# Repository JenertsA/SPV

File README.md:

# SPV
Darbi un piemēri Siguldas pilsētas vidusskolas Robtou tehnoloģiju novirzienam

## Ko šeit var atrast?
Pakāpeniski šeit tiks ievietoti darbi un piemēri, kas saistīti ar:
- elektornikas pamatiem
- Arduino programmēšanu
- spiesto plašu izstrādi Eagle programmā
- vienkāršu iekārtu izstrādi

jebkurš interesents ir lapini aicināts piedāvāt savus uzlabojumus un ieteikumus materiāliem, kas šeit atrodami

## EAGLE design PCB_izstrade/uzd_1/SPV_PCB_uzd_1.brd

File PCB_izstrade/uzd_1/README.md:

# Uzdevums   

Lai atvieglotu pirmās spiestās plates izstrādi Tev jau ir dota strādājoša shēma, kurā
izmantotas zināmi un pārbaudīti komponenšu *footprint*. Iekārta ir pavisam vienārš divu tranzistoru __multivibrators__.

Tev jāizgatavo spiestā plate cilvēkeim, kas __grib iemācīties lodēt__, tāpēc uz plates tiek lietotas lielas, *THD* detaļas.
Izvietotjot kompoenetes ņem vērā to, ka tās lodēs pilnīgi dažadi cilvēki,
dažādos vecumos un ar dažādām prasmēm. Lai salodētā iekārta nebūtu vienkārši izmetama, __izdomā tai interesantu formu__, 
ievieto atbilstoša izmēra urbumu un paredzi komonenšu izvietojumu tā, lai t __varētu lietot kā atslēgas piekariņu__.

## nosacījumi
- plate ir divu slāņu (1p.)
- platei ir neregulāra forma, kas iekļaujas izmēros (3p.)
- ir izpldīts uzdevums, kas atrodams .sch failā kā teksts (3p.)
- ir lietots jēgpilns celiņu platums, kura izmērs ir metrisks (2p.)
- *silkscreen* norādi gadu, kad izstrādāta plate(1p.)
- *silkscreen* atrodams autora vārds vai izdomāts logo (2p.)
- uzaksti, kas atrodas uz *silkscreen* ir izkārtoti un tādā izmērā, kas palīdz cilvēkam ievietot pareizi detaļas (3p.)
- platē tiek lietoti *poligoni*, kas savieno detaļas(2p.)
- celiņi uz plates vilki sistemātiski, lietojot 45° leņķi (3p.)

### papildus uzdevumi
Starp Eagle un Fusion 360 pastāv iesēja savienot projektus. </br>
Ievieto jaunizveidoto plati Fusion360 un uztaisīt detalizētu modeli
kā piekariņš izskatīsies realitātē 

Sagatavo *GERBER* failus pirkš ražotāja

Izveido pirmās reizes pamācību cilvēkam, kas mēģināt lodēt Tavu piekariņu, kas kur jāsprauž un kā kas jādara. 

### paturi prātā
- platei jābūt nelielai, bet ne tika mazai, lai to ir grūti lodēt (iekļaujies 30x30 mm, bet ne lielāku kā 60x30 mm)
- attālumam starp komponentēm jābūt tik lielam, lai, lodējot tās, samazinātu risku izveidot *solder bridge*
- Tev nepieciešami abi faili, gan .sch, gan .brd. Starp tiem pastāv sasaiste, kas lieti noder plates izstrādē.

### *lietotie termini*

*__footprint__* - urbumi vai laukumu izmērs un novietojums konkrētajai detaļa, lai tā varētu tikt montēta platē.

*__THD__* - no angļu valodas *Through-hole technology/devices* detaļas, kas tiek montētas urbumos. 

*__silkscreen__* - uzraksti, kas, parasti baltā krāsā, uzdrukāti uz plates. Tie tiek lietoti, lai marķētu detļau novietojumu, nosaukumu,
retāk detaļu vērtībām. Silkscreens tiek lietotas arī, lai piešķirtu platēm unikālāku izskatu. 

*__poligoni__* - vara pildījumi platē, ar kuru palīdzibu tiek aizstāta viena vai vairāku celiņu vilkšana. Tipiski ir visu plates varu izmantot kā lielu zemes poligonu - *ground plane*

*__GERBER__* - failu kopums, ko nosūta ražotājam, kas izgatavo plates. gerber faili ir de facto standarta faili, kurus atvērs jebkurš ražotājs jebkurā veitā un spēs sagatavot plati ražošanai.

*__solder bridge__* - lodējot divus blakus esošus kontaktus, alva starp lodējumiem saplūst un veido nevēlamu īssavienojumu.

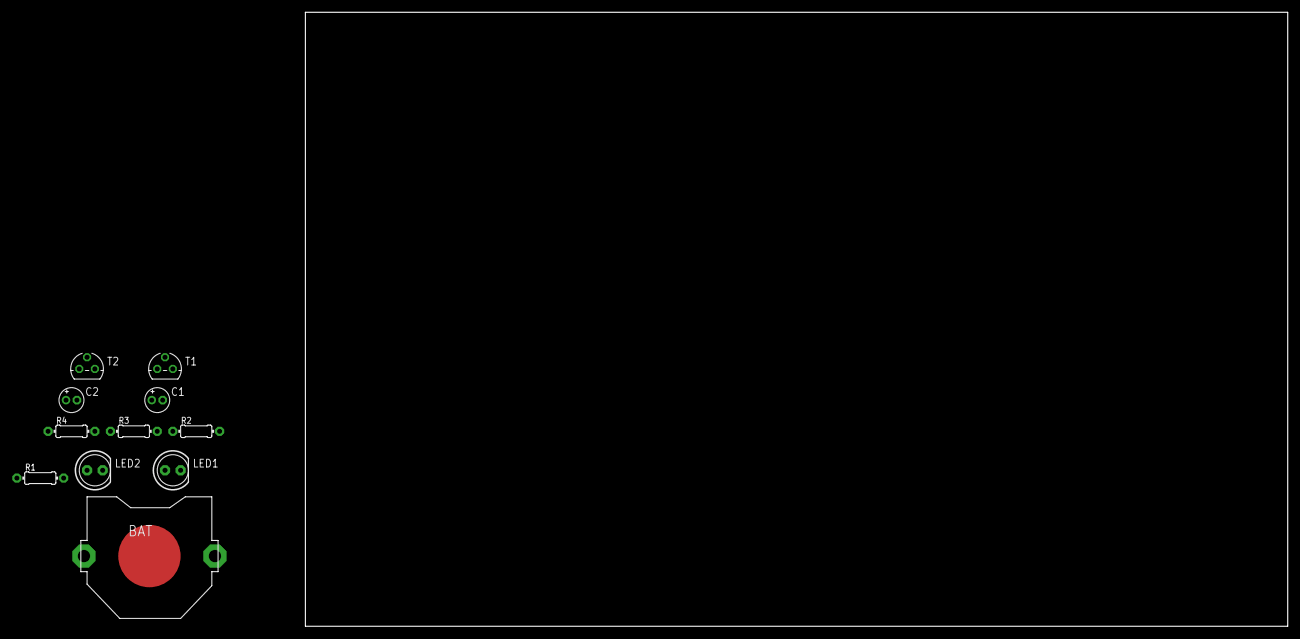
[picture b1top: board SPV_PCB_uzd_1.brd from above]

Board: 2 copper layers, 160.0 x 100.0 mm, 11 parts (0 on the bottom side), 8 nets, no tracks yet.

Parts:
BAT: CR2032-THRU
C1, C2: 10uF 6.3V; E1,8-4
LED1, LED2: LED5MM
R1, R2: 47K; R-7.5MM
R3, R4: 100R; R-7.5MM
T1, T2: BC547; TO92

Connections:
GND: BAT.+1, BAT.+2, T1.1, T2.1
unnamed: C1.-, R1.1, T2.2
unnamed: C1.+, R3.1, T1.3
unnamed: LED1.K, R3.2
unnamed: C2.+, R4.1, T2.3
unnamed: C2.-, R2.1, T1.2
unnamed: LED2.K, R4.2
V+: BAT.-, LED1.A, LED2.A, R1.2, R2.2

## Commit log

2020-03-23 eagle files added
2020-03-23 Create task instructions
2020-04-29 Create uzd_1
